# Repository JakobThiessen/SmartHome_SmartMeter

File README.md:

# SmartHome_SmartMeter
Smart Meter ist ein Modul (ESP32 + ETH) mit 6 Eingängen, die beliebig, über ein Script, konfiguriert werden können.

IR_Sensor

# Tasmota Einrichtung

Hier findest du die Dokumentation: [settings](/document/Tasmota_Einrichtung.md)

Hier findest du vorkompilierte firmware: [precompiled](/firmware_precompiled)

# Gehäuse

Gehäuseunterteil - BC 35,6 https://www.phoenixcontact.com/de-ch/produkte/einbaugehaeuseunterteil-bc-356-ut-hbus-bk-2896254
Gehäuseoberteil - BC 35,6 https://www.phoenixcontact.com/de-ch/produkte/einbaugehaeuseoberteil-bc-356-ot-u11-kmgy-2896034

# Bauteile
ETH Stecker HR911105A
https://lcsc.com/product-detail/Ethernet-Connectors-Modular-Connectors-RJ45-RJ11_HANRUN-Zhongshan-HanRun-Elec-HR911105A_C12074.html

PHY LAN8720A    https://www.microchip.com/en-us/product/LAN8720A
https://lcsc.com/product-detail/Ethernet-ICs_Microchip-Tech-LAN8720A-CP-TR_C45223.html 

# Pinout

| Label | IO    | Beschreibung      |                          |
|-------|-------|-------------------|--------------------------|
| IN01  | IO01  | GPIO/TXD0         |                          |
| IN02  | IO03  | GPIO/RXD0         | 
| IN03  | IO05  | GPIO              | 
| IN04  | IO033 | GPIO/ADC_CH5      | used as Counter
| IN05  | IO016 | GPIO/RXD_2        | used for SML (See Script)
| AIN   | IO034 | GPIO/ADC_CH6      | 

# Tasmota Pinconfiguration

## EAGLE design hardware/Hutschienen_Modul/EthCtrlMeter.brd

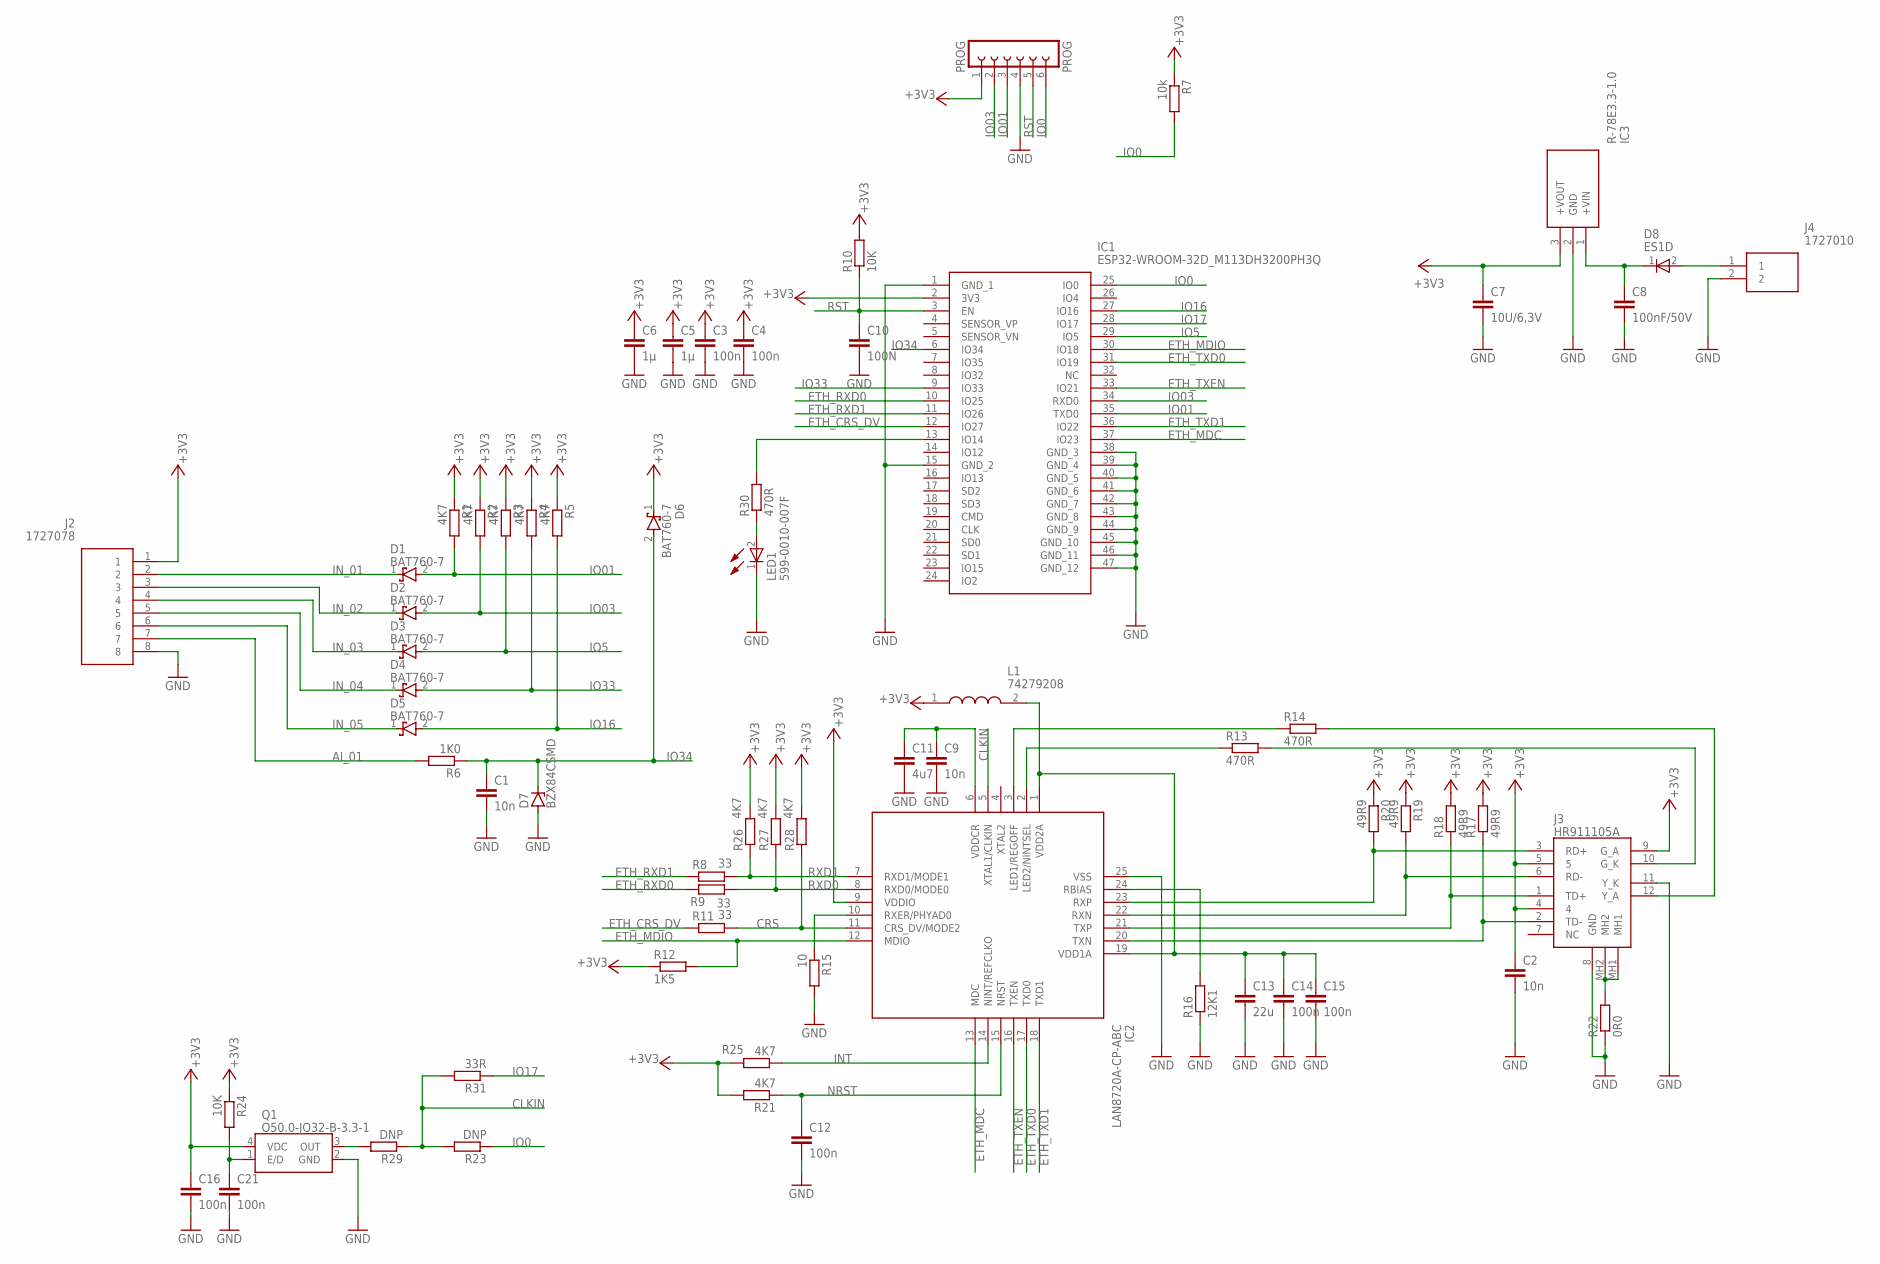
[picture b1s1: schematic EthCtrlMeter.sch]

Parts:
C1, C2, C9: 10n; C0603
C3, C4, C12, C14, C15, C16, C21: 100n; C0603
C5, C6: 1µ; C0603
C7: 10U/6,3V; C0603
C8: 100nF/50V; C0603
C10: 100N; C0603
C11: 4u7; C0603
C13: 22u; C0603
D1, D2, D3, D4, D5, D6: BAT760-7; SOD2513X120N
D7: BZX84CSMD; TO236
D8: ES1D; SODFL3618X143N
IC1: ESP32-WROOM-32D_M113DH3200PH3Q; ESP32WROOM32DM113DH3200PH3Q0
IC2: LAN8720A-CP-ABC; QFN50P400X400X100-25N
IC3: R-78E3.3-1.0; R78E3310
J2: 1727078
J3: HR911105A
J4: 1727010
L1: 74279208; CAPC2012X90N
LED1: 599-0010-007F; LEDM168X70N
PROG: PROG; FE06
Q1: O50.0-JO32-B-3.3-1; O200JO32B1V31T1LF
R1, R2, R3, R4, R5, R21, R25, R26, R27, R28: 4K7; R0603
R6: 1K0; R0603
R7: 10k; R0603
R8, R9, R11: 33; R0603
R10, R24: 10K; R0603
R12: 1K5; R0603
R13, R14, R30: 470R; R0603
R15: 10; R0603
R16: 12K1; R0603
R17, R18, R19, R20: 49R9; R0603
R22: 0R0; R0603
R23, R29: DNP; R0603
R31: 33R; R0603

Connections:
+3V3: C2.1, C3.1, C4.1, C5.1, C6.1, C7.1, C16.1, D6.1 (K), IC1.2 (3V3), IC2.9 (VDDIO), IC3.3 (+VOUT), J2.1, J3.4, J3.5, J3.9 (G_A), L1.1, PROG.1, Q1.4 (VDC), R1.1, R2.1, R3.1, R4.1, R5.1, R7.1, R10.2, R12.1, R17.2, R18.2, R19.1, R20.1, R21.2, R24.1, R25.2, R26.2, R27.2, R28.2
AI_01: J2.7, R6.2
CLKIN: IC2.5 (XTAL1/CLKIN), R23.2, R29.1, R31.2
CRS: IC2.11 (CRS_DV/MODE2), R11.2, R28.1
ETH_CRS_DV: IC1.12 (IO27), R11.1
ETH_MDC: IC1.37 (IO23), IC2.13 (MDC)
ETH_MDIO: IC1.30 (IO18), IC2.12 (MDIO), R12.2
ETH_PHY_PWR: C21.1, Q1.1 (E/D), R24.2
ETH_RXD0: IC1.10 (IO25), R9.1
ETH_RXD1: IC1.11 (IO26), R8.1
ETH_TXD0: IC1.31 (IO19), IC2.17 (TXD0)
ETH_TXD1: IC1.36 (IO22), IC2.18 (TXD1)
ETH_TXEN: IC1.33 (IO21), IC2.16 (TXEN)
GND: C1.2, C2.2, C3.2, C4.2, C5.2, C6.2, C7.2, C8.2, C9.2, C10.2, C11.2, C12.2, C13.2, C14.2, C15.2, C16.2, C21.2, D7.A, IC1.1 (GND_1), IC1.15 (GND_2), IC1.38 (GND_3), IC1.39 (GND_4), IC1.40 (GND_5), IC1.41 (GND_6), IC1.42 (GND_7), IC1.43 (GND_8), IC1.44 (GND_9), IC1.45 (GND_10), IC1.46 (GND_11), IC1.47 (GND_12), IC2.25 (VSS), IC3.2 (GND), J2.8, J3.8 (GND), J3.11 (Y_K), J4.2, LED1.1 (K), PROG.4, Q1.2 (GND), R15.2, R16.1, R22.1
INT: IC2.14 (NINT/REFCLKO), R25.1
IN_01: D1.1 (K), J2.2
IN_02: D2.1 (K), J2.3
IN_03: D3.1 (K), J2.4
IN_04: D4.1 (K), J2.5
IN_05: D5.1 (K), J2.6
IO0: IC1.25 (IO0), PROG.6, R7.2, R23.1
IO01: D1.2 (A), IC1.35 (TXD0), PROG.3, R1.2
IO03: D2.2 (A), IC1.34 (RXD0), PROG.2, R2.2
IO5: D3.2 (A), IC1.29 (IO5), R3.2
IO16: D5.2 (A), IC1.27 (IO16), R5.2
IO17: IC1.28 (IO17), R31.1
IO33: D4.2 (A), IC1.9 (IO33), R4.2
IO34: C1.1, D6.2 (A), D7.C, IC1.6 (IO34), R6.1
unnamed: IC1.13 (IO14), R30.2
unnamed: IC2.20 (TXN), J3.2 (TD-), R17.1
unnamed: IC2.22 (RXN), J3.6 (RD-), R19.2
unnamed: IC2.23 (RXP), J3.3 (RD+), R20.2
unnamed: J3.12 (Y_A), R14.2
unnamed: J3.10 (G_K), R13.2
unnamed: C8.1, D8.1 (K), IC3.1 (+VIN)
unnamed: Q1.3 (OUT), R29.2
unnamed: J3.MH1, J3.MH2, R22.2
unnamed: D8.2 (A), J4.1
unnamed: LED1.2 (A), R30.1
unnamed: C13.1, C14.1, C15.1, IC2.1 (VDD2A), IC2.19 (VDD1A), L1.2
unnamed: C9.1, C11.1, IC2.6 (VDDCR)
unnamed: IC2.2 (LED2/NINTSEL), R13.1
unnamed: IC2.3 (LED1/REGOFF), R14.1
unnamed: IC2.10 (RXER/PHYAD0), R15.1
unnamed: IC2.21 (TXP), J3.1 (TD+), R18.1
unnamed: IC2.24 (RBIAS), R16.2
NRST: C12.1, IC2.15 (NRST), R21.1
RST: C10.1, IC1.3 (EN), PROG.5, R10.1
RXD0: IC2.8 (RXD0/MODE0), R9.2, R27.1
RXD1: IC2.7 (RXD1/MODE1), R8.2, R26.1

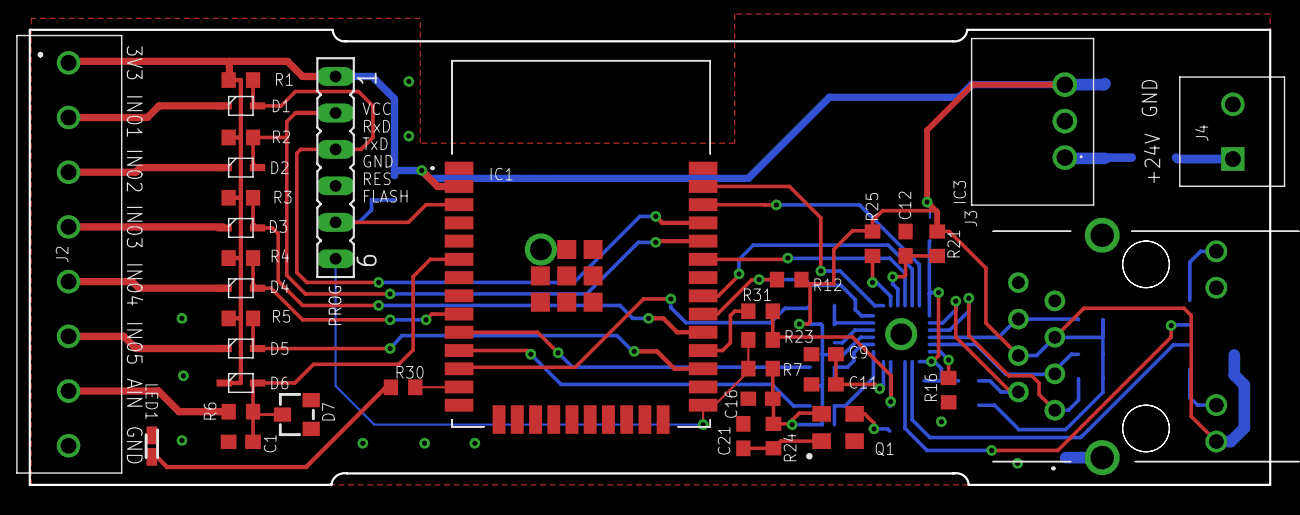
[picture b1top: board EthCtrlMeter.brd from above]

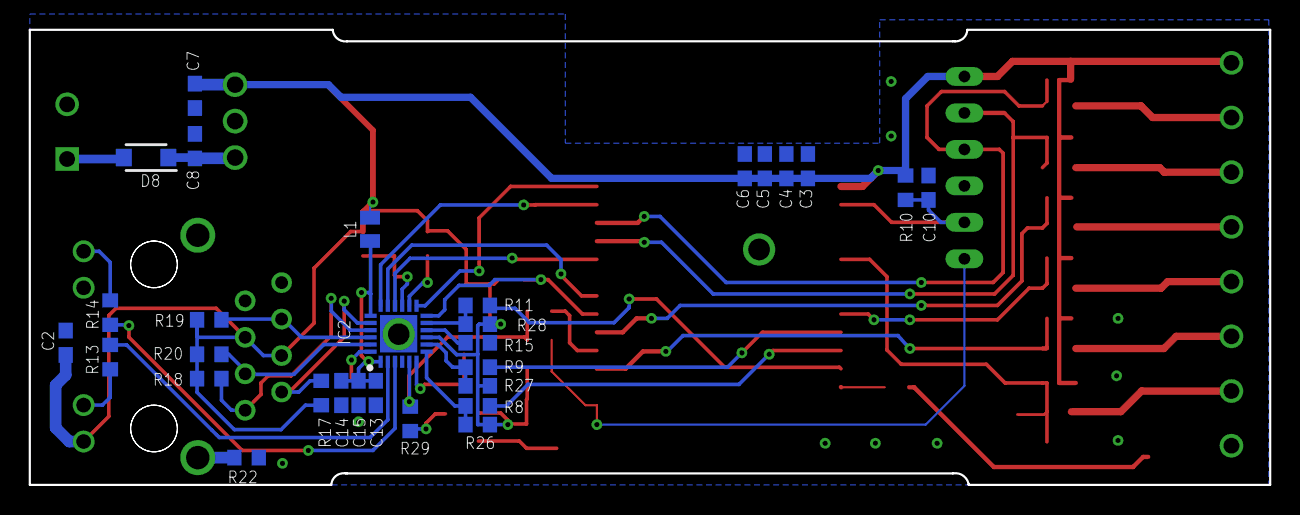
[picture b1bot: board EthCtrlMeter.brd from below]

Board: 2 copper layers, 86.4 x 31.7 mm, 66 parts (30 on the bottom side), 50 nets.

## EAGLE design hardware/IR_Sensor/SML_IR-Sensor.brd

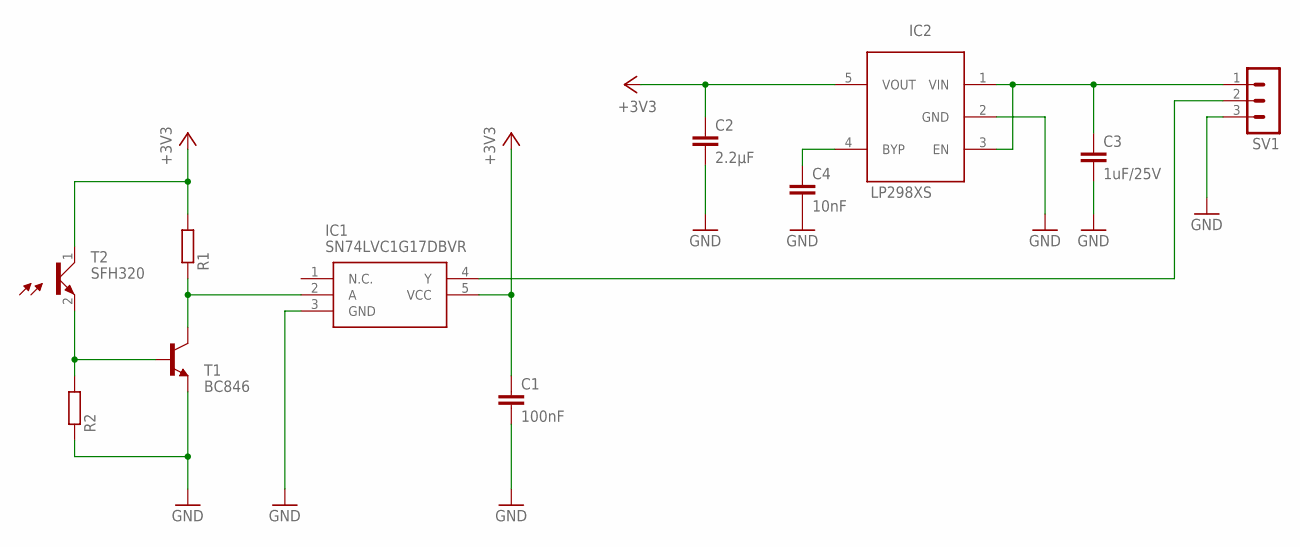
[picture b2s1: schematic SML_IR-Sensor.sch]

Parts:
C1: 100nF; C0603
C2: 2.2µF; C0603
C3: 1uF/25V; C0603
C4: 10nF; C0603
IC1: SN74LVC1G17DBVR; SOT95P280X145-5N
IC2: LP298XS; SOT23-5L
R1, R2: R-EU_R0603; R0603
SV1: MA03-1
T1: BC846; SOT23
T2: SFH320; LEDM3528X210N

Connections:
+3V3: C1.1, C2.1, IC1.5 (VCC), IC2.5 (VOUT), R1.2, T2.1 (C)
GND: C1.2, C2.2, C3.2, C4.2, IC1.3 (GND), IC2.2 (GND), R2.1, SV1.3, T1.2 (E)
unnamed: IC1.2 (A), R1.1, T1.3 (C)
unnamed: IC1.4 (Y), SV1.2
unnamed: R2.2, T1.1 (B), T2.2 (E)
unnamed: C3.1, IC2.1 (VIN), IC2.3 (EN), SV1.1
unnamed: C4.1, IC2.4 (BYP)

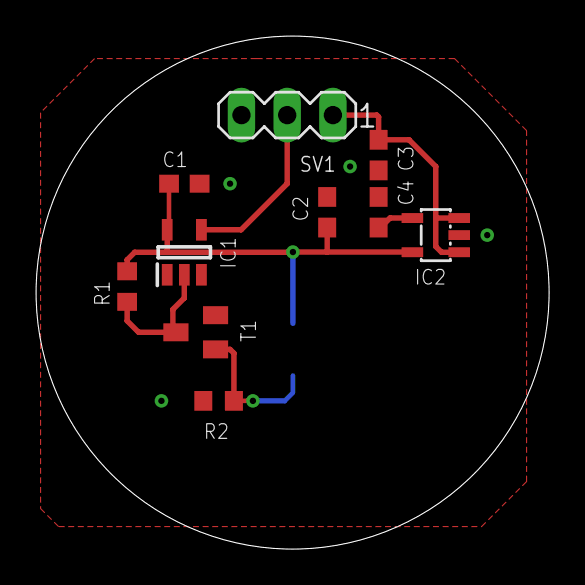
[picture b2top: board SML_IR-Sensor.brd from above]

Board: 2 copper layers, 28.5 x 28.5 mm, 11 parts (1 on the bottom side), 7 nets.

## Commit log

2022-02-09 hardware hinzugefügt
2022-02-09 3d model und bilder hinzugefügt
2022-02-09 doc hinzugefügt
2022-05-29 add pdf files
2022-05-30 initial
2022-05-30 Rename TasmotaSML Einrichtung.md to Tasmota Einrichtung.md
2022-05-30 Rename Tasmota Einrichtung.md to Tasmota_Einrichtung.md
2022-08-01 Update Tasmota_Einrichtung.md
    openHAB Beispiel hinzugefügt
2022-08-09 Update Tasmota_Einrichtung.md
    Scripting Beispiele ergänzt
2022-08-17 neue Ordner mit 3d Model zum drucken
2025-10-21 Tasmota 15.0.1 inkl. Scripts, SML, Matter
